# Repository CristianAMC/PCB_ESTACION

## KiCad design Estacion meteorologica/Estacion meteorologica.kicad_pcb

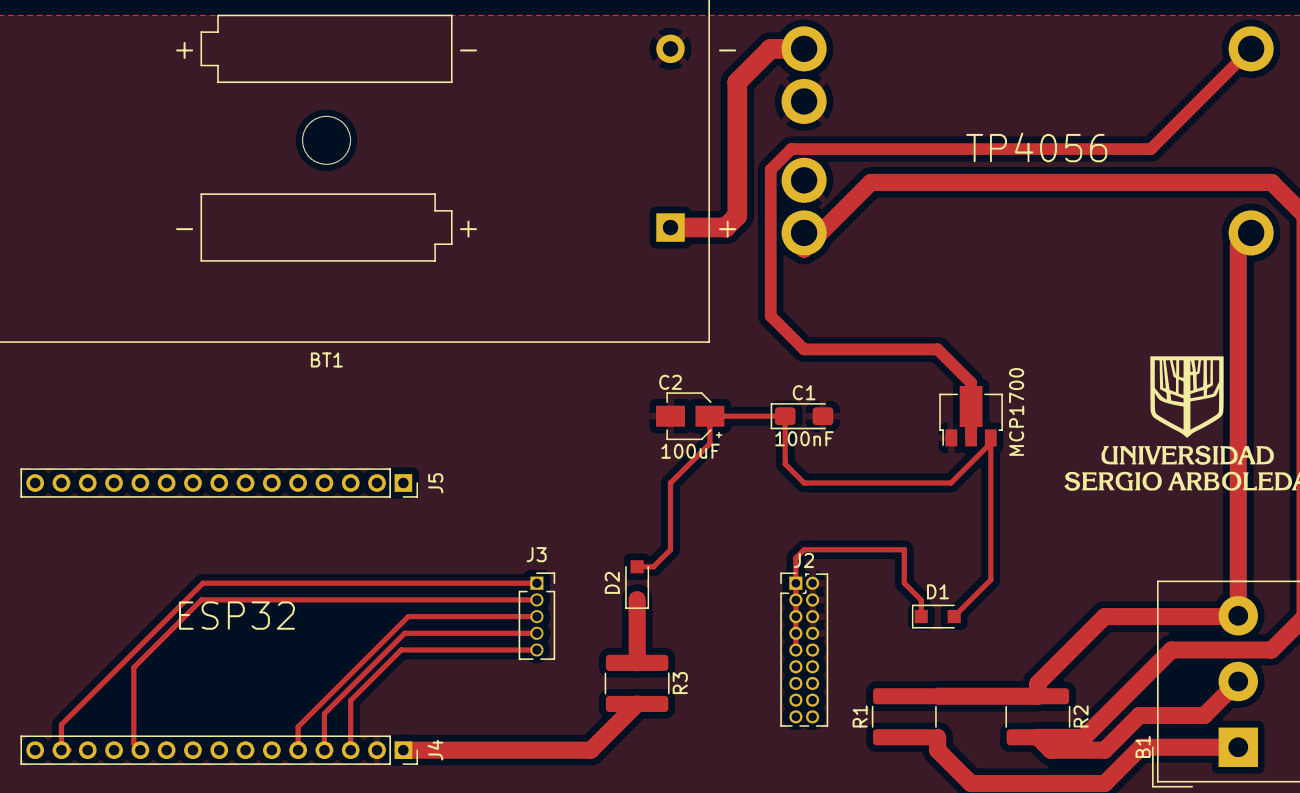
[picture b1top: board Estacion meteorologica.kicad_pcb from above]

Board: 2 copper layers, 15 parts (0 on the bottom side), 15 nets.

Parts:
100uF: C_Polarized_US; CP_Elec_3x5.3
B1: Solar panel 6V; Altech_AK300_1x03_P5.00mm_45-Degree
BT1: Battery_Cell; BatteryHolder_MPD_BC2AAPC_2xAA
C1: 100nF; CP_EIA-3216-18_Kemet-A_Pad1.58x1.35mm_HandSolder
D1, D2: 1N4001; D_SOD-323_HandSoldering
J2: Conn_2Rows-09Pins; PinHeader_2x09_P1.27mm_Vertical
J3: Conn_01x05; PinSocket_1x05_P1.27mm_Vertical
J4: Conn_01x15; PinSocket_1x15_P2.00mm_Vertical
J5: ESP32; PinSocket_1x15_P2.00mm_Vertical
R1, R2: 2k; R_1218_3246Metric_Pad1.22x4.75mm_HandSolder
R3: 47; R_1218_3246Metric_Pad1.22x4.75mm_HandSolder
U4: TP4056
U7: MCP1700; SOT-89-3

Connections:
/Data_DHT: J3.5, J4.3
/Data_KY: J3.3, J4.5
/Data_YL: J3.4, J4.4
/SCL_BMP: J3.1, J4.14
/SDA_BMP: J3.2, J4.11
/VBAT: BT1.1 (+), U4.4 (BAT_+)
/VBMP: D1.1 (K), J2.1, J2.3, J2.5, J2.7, J2.9
/Vout: 100uF.1, C1.1, D1.2 (A), D2.2 (A), U7.3 (VO)
GND: 100uF.2, BT1.2 (-), C1.2, J2.2, J2.4, J2.6, J2.8, J4.2, U4.5 (BAT_-), U4.6 (OUT-), U7.1 (GND)
unnamed: D2.1 (K), R3.1
unnamed: B1.1, R1.1
unnamed: B1.2, R2.2, U4.2 (-)
unnamed: B1.3, R1.2, R2.1, U4.1 (+)
unnamed: J4.1, R3.2
unnamed: U4.3 (OUT_+), U7.2 (VI)

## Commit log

2022-05-23 Add files via upload
    Adicion del proyecto
